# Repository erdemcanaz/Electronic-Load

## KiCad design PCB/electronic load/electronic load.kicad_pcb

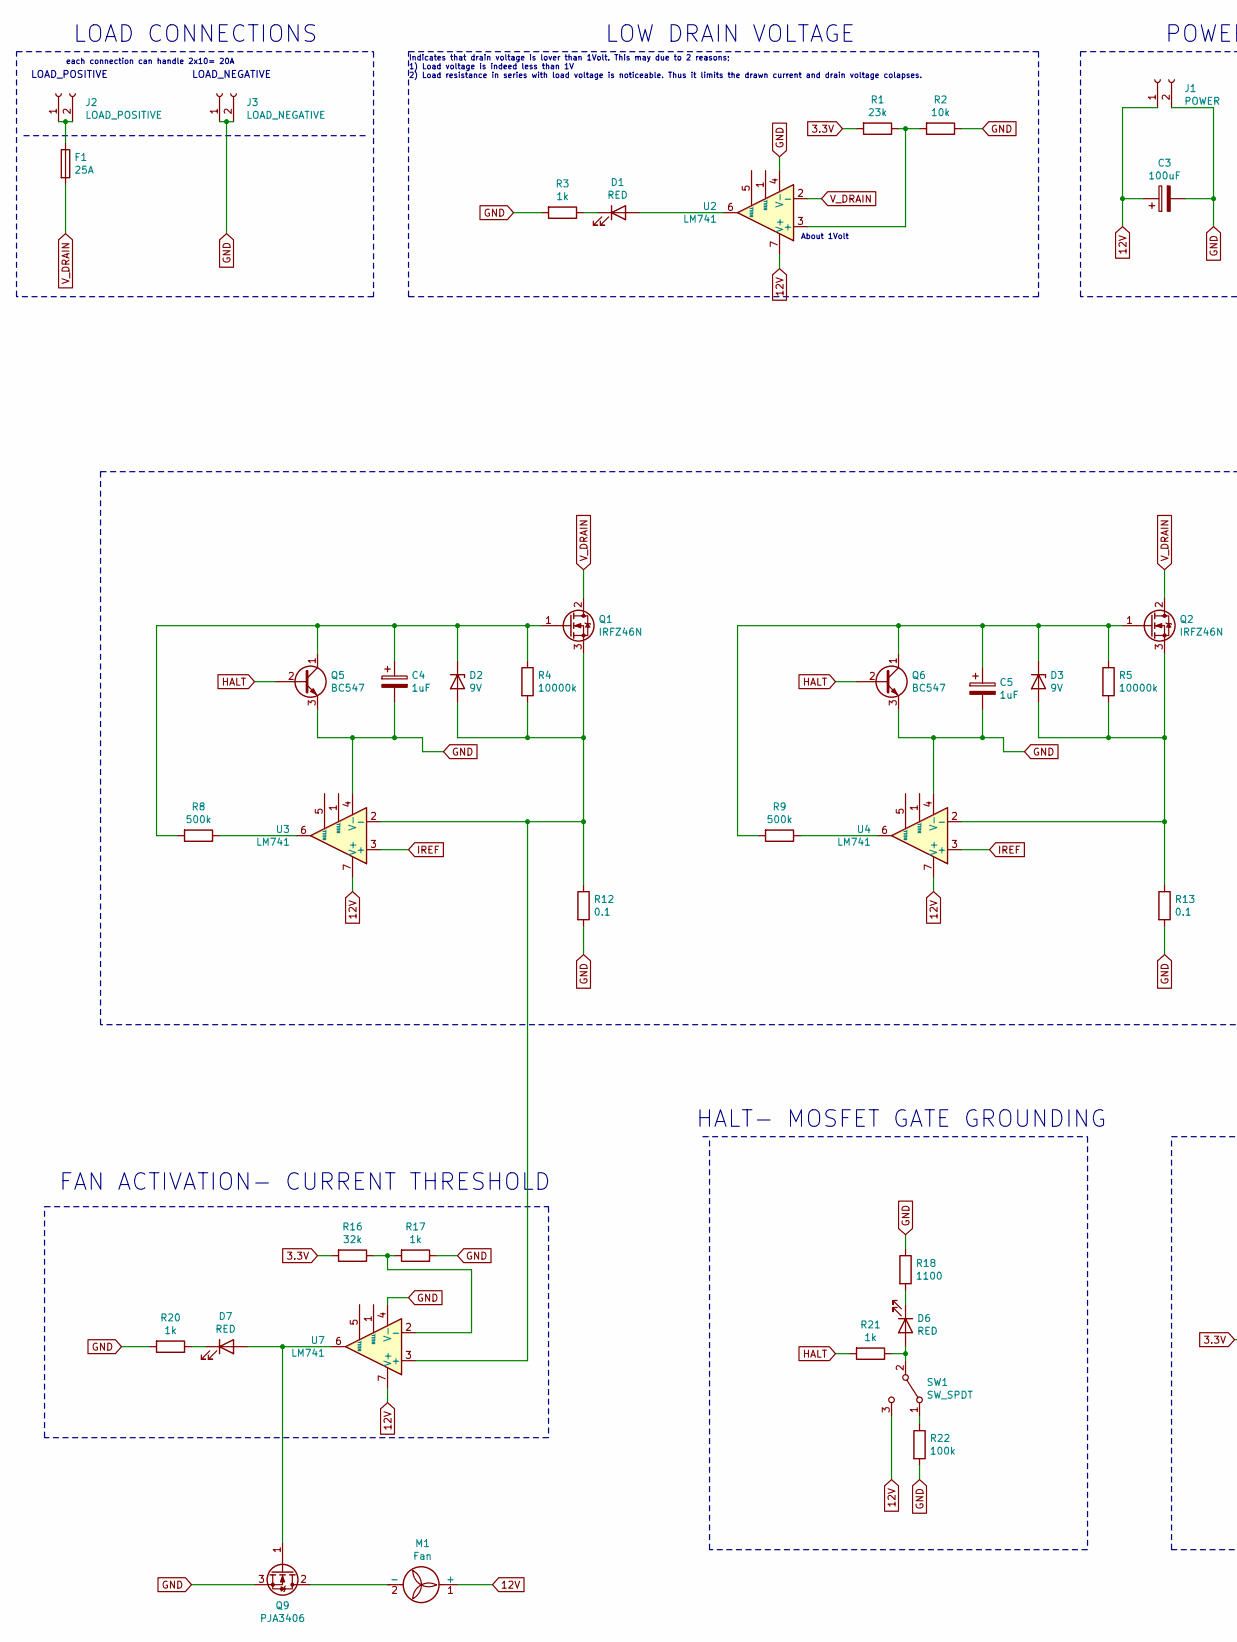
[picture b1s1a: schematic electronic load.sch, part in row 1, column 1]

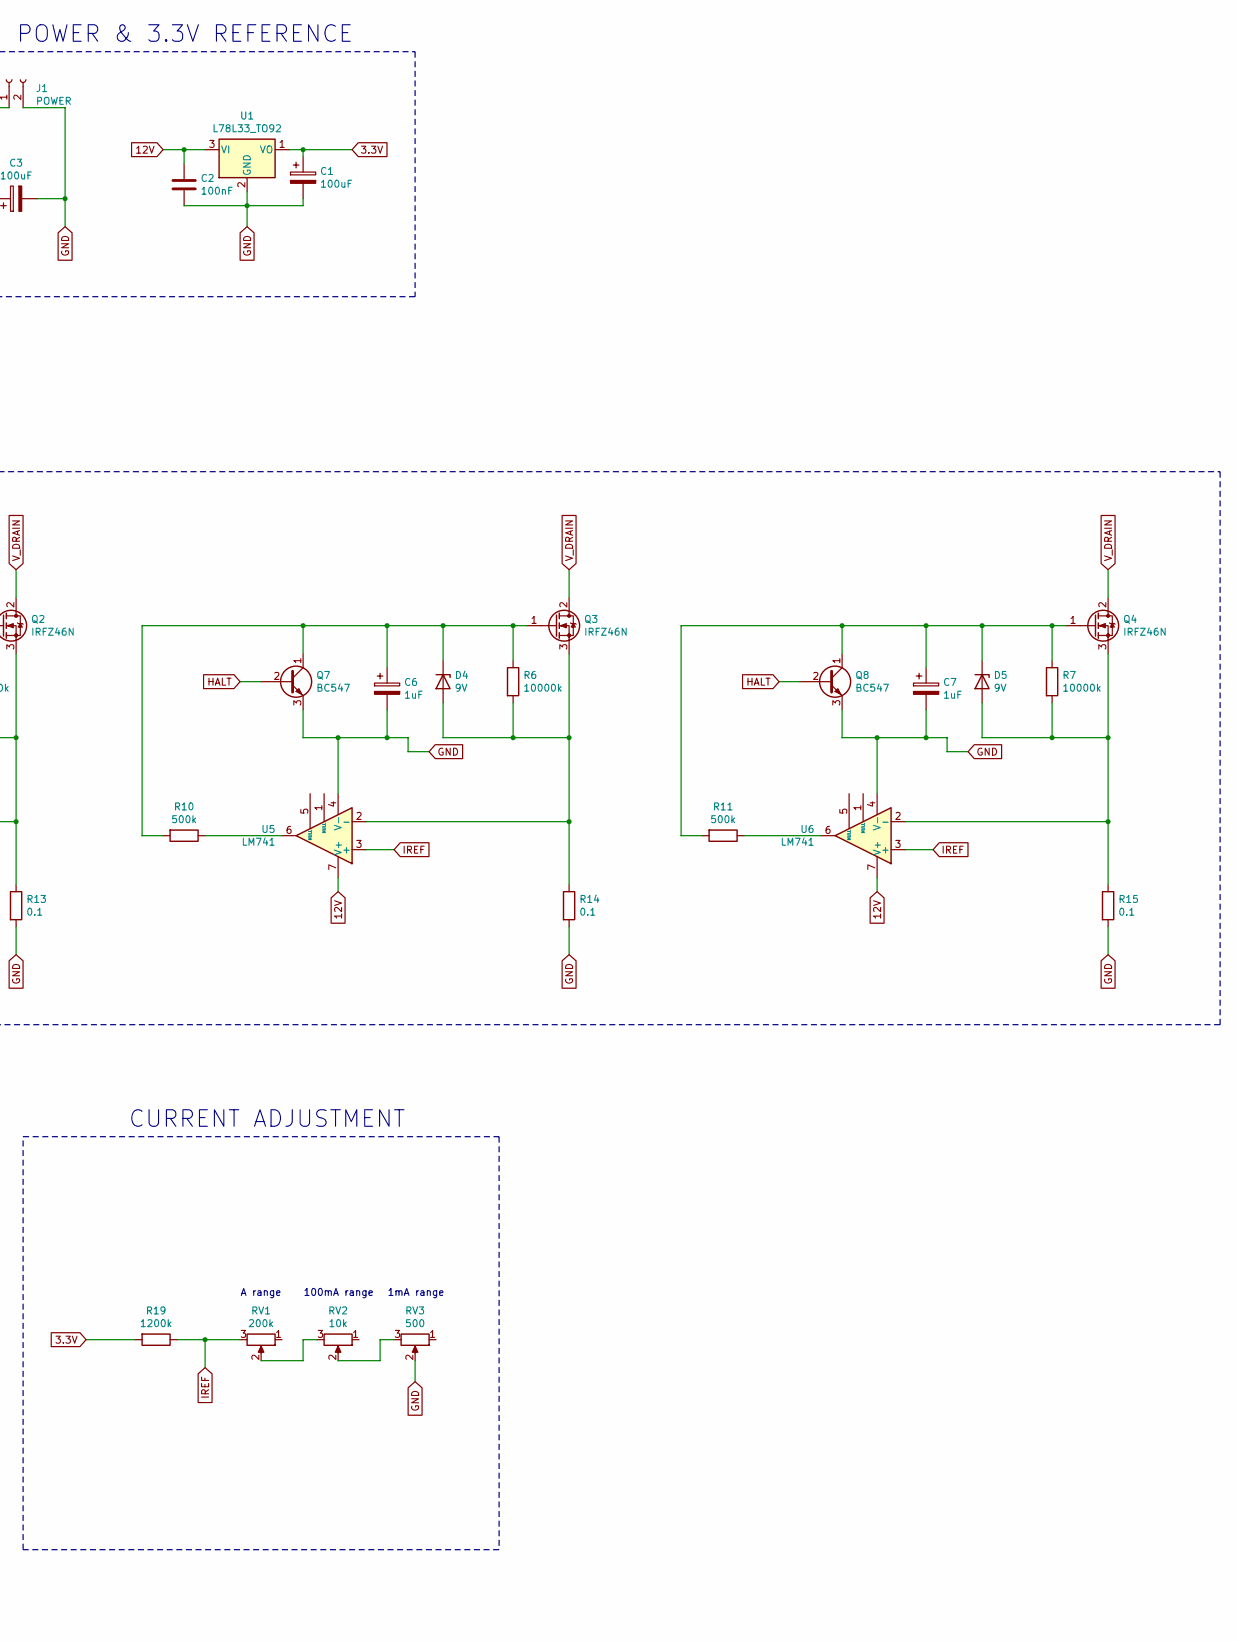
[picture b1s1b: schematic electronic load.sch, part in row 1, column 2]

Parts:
C1, C3: 100uF; CP_Radial_D5.0mm_P2.00mm
C2: 100nF; CP_Radial_D5.0mm_P2.00mm
C4, C5, C6, C7: 1uF; CP_Radial_D5.0mm_P2.00mm
D1, D6, D7: RED; LED_D3.0mm_FlatTop
D2, D3, D4, D5: 9V; D_A-405_P12.70mm_Horizontal
F1: 25A; fuse
J1: POWER; klemens 2li
J2: LOAD_POSITIVE; klemens 2li
J3: LOAD_NEGATIVE; klemens 2li
M1: Fan; PinHeader_1x02_P2.00mm_Vertical
Q1, Q2, Q3, Q4: IRFZ46N; TO-220-3_Horizontal_TabUp
Q5, Q6, Q7, Q8: BC547; TO-92_Inline_Wide
Q9: PJA3406; SOT-23
R1: 23k; R_Axial_DIN0207_L6.3mm_D2.5mm_P7.62mm_Horizontal
R2: 10k; R_Axial_DIN0207_L6.3mm_D2.5mm_P7.62mm_Horizontal
R3, R17, R20, R21: 1k; R_Axial_DIN0207_L6.3mm_D2.5mm_P7.62mm_Horizontal
R4, R5, R6, R7: 10000k; R_Axial_DIN0207_L6.3mm_D2.5mm_P7.62mm_Horizontal
R8, R9, R10, R11: 500k; R_Axial_DIN0207_L6.3mm_D2.5mm_P7.62mm_Horizontal
R12, R13, R14, R15: 0.1; R_Axial_Power_L25.0mm_W9.0mm_P27.94mm
R16: 32k; R_Axial_DIN0207_L6.3mm_D2.5mm_P7.62mm_Horizontal
R18: 1100; R_Axial_DIN0207_L6.3mm_D2.5mm_P7.62mm_Horizontal
R19: 1200k; R_Axial_DIN0207_L6.3mm_D2.5mm_P7.62mm_Horizontal
R22: 100k; R_Axial_DIN0207_L6.3mm_D2.5mm_P7.62mm_Horizontal
RV1: 200k; pot
RV2: 10k; pot
RV3: 500; pot
SW1: SW_SPDT; PinHeader_1x03_P2.00mm_Horizontal
U1: L78L33_TO92; TO-92_Inline_Wide
U2, U3, U4, U5, U6, U7: LM741; DIP-8_W7.62mm

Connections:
3.3V: C1.1, R1.2, R16.2, R19.2, U1.1 (VO)
12V: C2.1, C3.1, J1.1, M1.1 (+), SW1.3 (C), U1.3 (VI), U2.7 (V+), U3.7 (V+), U4.7 (V+), U5.7 (V+), U6.7 (V+), U7.7 (V+)
GND: C1.2, C2.2, C3.2, C4.2, C5.2, C6.2, C7.2, J1.2, J3.1, J3.2, Q5.3 (E), Q6.3 (E), Q7.3 (E), Q8.3 (E), Q9.3 (S), R2.1, R3.2, R12.2, R13.2, R14.2, R15.2, R17.1, R18.1, R20.2, R22.2, RV3.2, U1.2 (GND), U2.4 (V-), U3.4 (V-), U4.4 (V-), U5.4 (V-), U6.4 (V-), U7.4 (V-)
HALT: Q5.2 (B), Q6.2 (B), Q7.2 (B), Q8.2 (B), R21.2
IREF: R19.1, RV1.3, U3.3 (+), U4.3 (+), U5.3 (+), U6.3 (+)
unnamed: C4.1, D2.1 (K), Q1.1 (G), Q5.1 (C), R4.1, R8.2
unnamed: C5.1, D3.1 (K), Q2.1 (G), Q6.1 (C), R5.1, R9.2
unnamed: C6.1, D4.1 (K), Q3.1 (G), Q7.1 (C), R6.1, R10.2
unnamed: C7.1, D5.1 (K), Q4.1 (G), Q8.1 (C), R7.1, R11.2
unnamed: D1.1 (K), R3.1
unnamed: D1.2 (A), U2.6
unnamed: D2.2 (A), Q1.3 (S), R4.2, R12.1, U3.2 (-), U7.3 (+)
unnamed: D3.2 (A), Q2.3 (S), R5.2, R13.1, U4.2 (-)
unnamed: D4.2 (A), Q3.3 (S), R6.2, R14.1, U5.2 (-)
unnamed: D5.2 (A), Q4.3 (S), R7.2, R15.1, U6.2 (-)
unnamed: D6.1 (K), R18.2
unnamed: D6.2 (A), R21.1, SW1.2 (B)
unnamed: D7.1 (K), R20.1
unnamed: D7.2 (A), Q9.1 (G), U7.6
unnamed: F1.1, J2.1, J2.2
unnamed: M1.2 (-), Q9.2 (D)
unnamed: R1.1, R2.2, U2.3 (+)
unnamed: R8.1, U3.6
unnamed: R9.1, U4.6
unnamed: R10.1, U5.6
unnamed: R11.1, U6.6
unnamed: R16.1, R17.2, U7.2 (-)
unnamed: R22.1, SW1.1 (A)
unnamed: RV1.2, RV2.3
unnamed: RV2.2, RV3.3
V_DRAIN: F1.2, Q1.2 (D), Q2.2 (D), Q3.2 (D), Q4.2 (D), U2.2 (-)

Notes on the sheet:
LOAD_POSITIVE
LOAD_NEGATIVE
LOAD CONNECTIONS
LOW DRAIN VOLTAGE
Indicates that drain voltage is lover than 1Volt. This may due to 2 reasons; 1) Load voltage is indeed less than 1V 2) Load resistance in series with load voltage is noticeable. Thus it limits the drawn current and drain voltage colapses.
About 1Volt
FAN ACTIVATION- CURRENT THRESHOLD
POWER & 3.3V REFERENCE
HALT- MOSFET GATE GROUNDING
A range
100mA range
1mA range
CURRENT ADJUSTMENT
each connection can handle 2x10= 20A

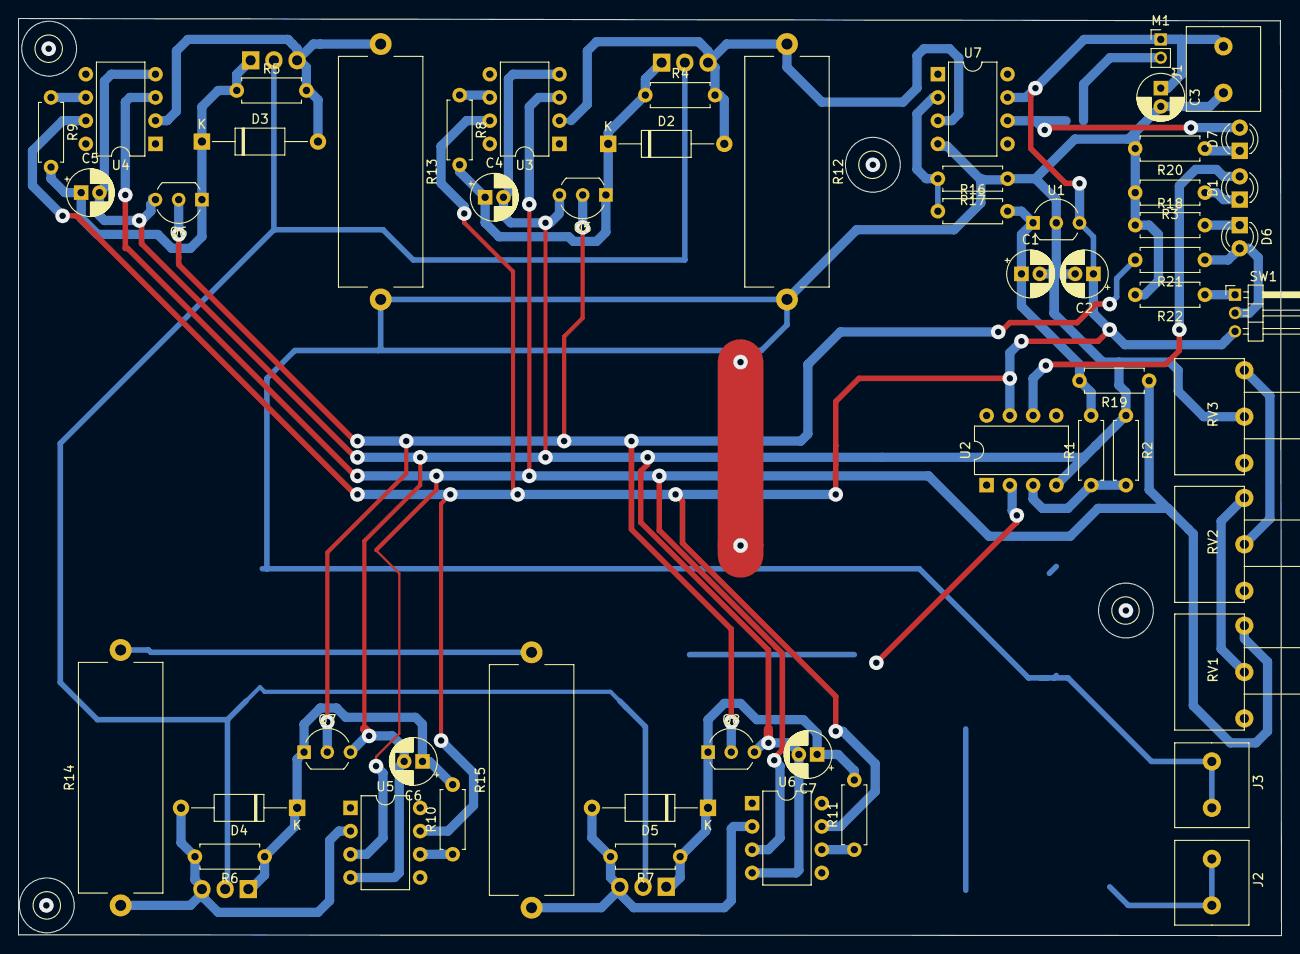
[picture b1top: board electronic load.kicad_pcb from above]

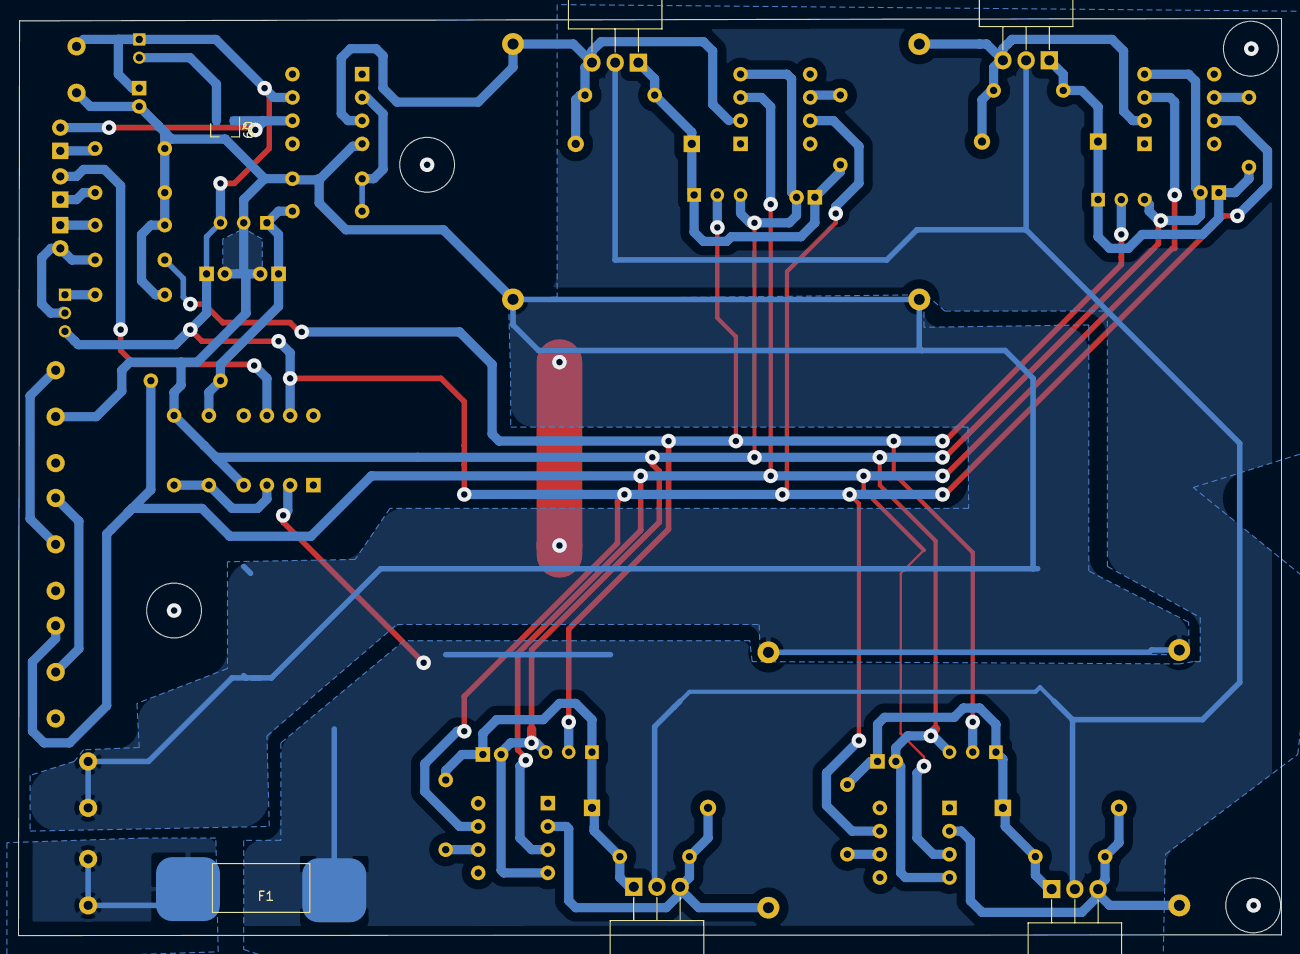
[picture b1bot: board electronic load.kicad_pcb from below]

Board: 2 copper layers, 138.2 x 100.3 mm, 61 parts (6 on the bottom side), 31 nets.

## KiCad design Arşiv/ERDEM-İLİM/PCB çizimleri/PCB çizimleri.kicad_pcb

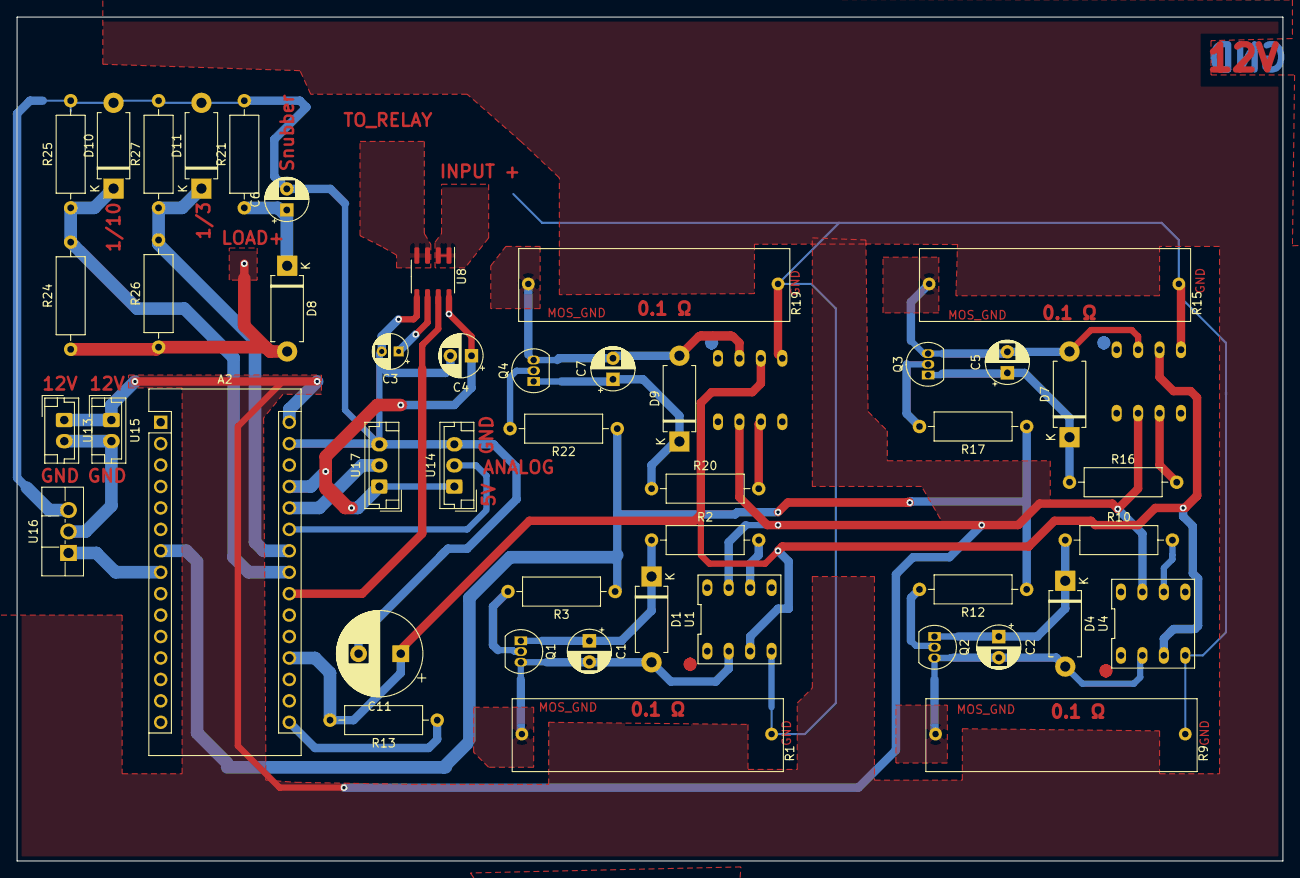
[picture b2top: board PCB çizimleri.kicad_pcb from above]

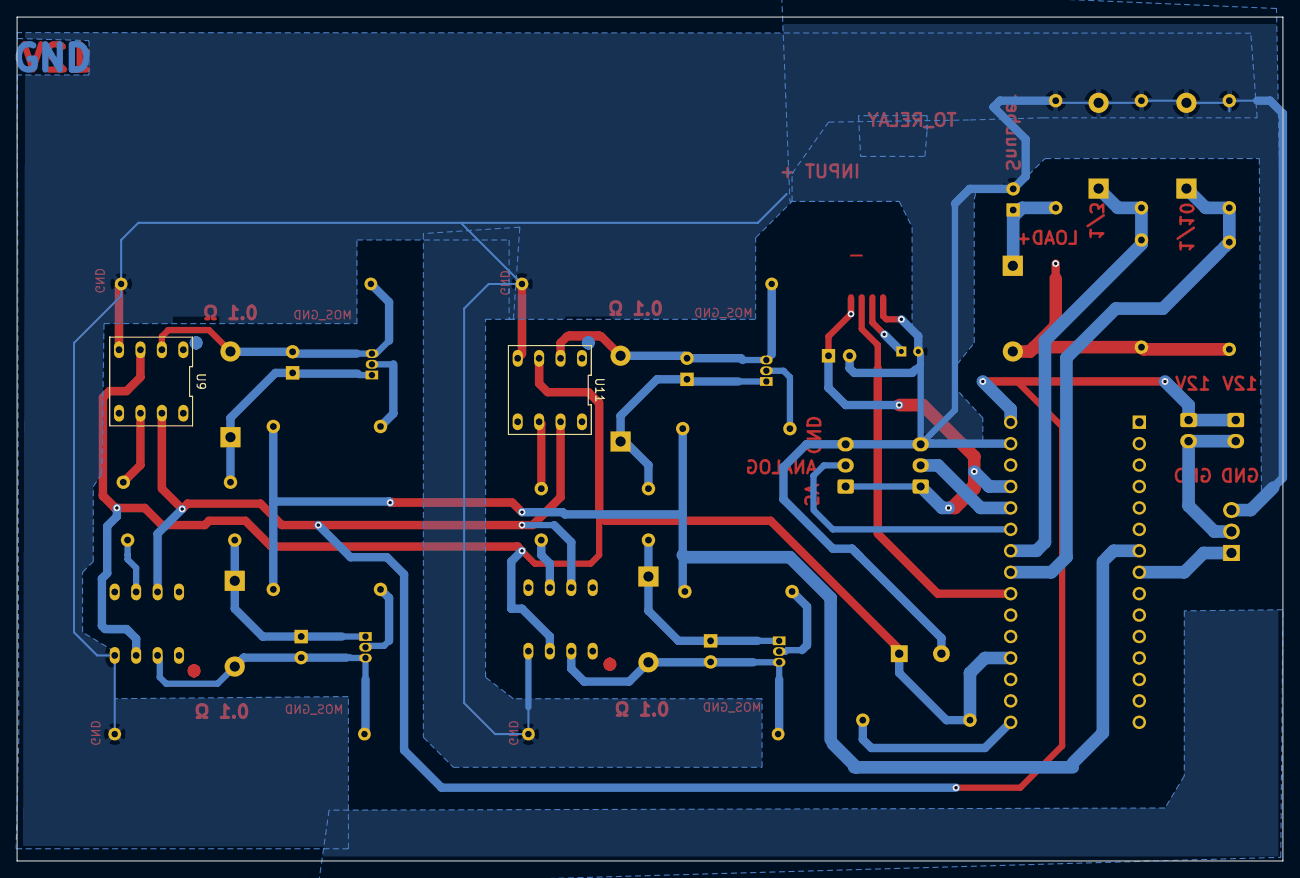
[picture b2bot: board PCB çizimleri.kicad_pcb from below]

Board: 2 copper layers, 150.0 x 100.0 mm, 48 parts (2 on the bottom side), 34 nets.

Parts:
A2: Arduino_Nano_v2.x; Arduino_Nano
C1, C2, C5, C7: 20uF; CP_Radial_D5.0mm_P2.50mm
C3: 1nF; CP_Radial_D4.0mm_P2.00mm
C4: 0.1uF; CP_Radial_D5.0mm_P2.50mm
C6: 100uF; CP_Radial_D5.0mm_P2.50mm
C11: 10uf; CP_Radial_D10.0mm_P5.00mm
D1, D4, D7, D9: 6.8; D_DO-15_P10.16mm_Horizontal
D8: D; D_DO-15_P10.16mm_Horizontal
D10, D11: 6.2V; D_DO-15_P10.16mm_Horizontal
Q1, Q2, Q3, Q4: BC547; TO-92_Inline
R1, R9, R15, R19: 0.1; 5W_tas
R2, R10, R16, R20: 330k; R_Axial_DIN0309_L9.0mm_D3.2mm_P12.70mm_Horizontal
R3, R12, R17, R22: 1k; R_Axial_DIN0309_L9.0mm_D3.2mm_P12.70mm_Horizontal
R13: 100k; R_Axial_DIN0309_L9.0mm_D3.2mm_P12.70mm_Horizontal
R21, R26: 20k; R_Axial_DIN0309_L9.0mm_D3.2mm_P12.70mm_Horizontal
R24: 36k; R_Axial_DIN0309_L9.0mm_D3.2mm_P12.70mm_Horizontal
R25: 4k; R_Axial_DIN0309_L9.0mm_D3.2mm_P12.70mm_Horizontal
R27: 10k; R_Axial_DIN0309_L9.0mm_D3.2mm_P12.70mm_Horizontal
U1, U4, U9, U11: LM741; DIP-8_296_ELL
U8: ACS712xLCTR-30A; SOIC-8_3.9x4.9mm_P1.27mm
U13, U15: fan; JST_EH_B2B-EH-A_1x02_P2.50mm_Vertical
U14, U17: LM35-LP; JST_EH_B3B-EH-A_1x03_P2.50mm_Vertical
U16: IRFZ44N; TO-220F-3_Vertical

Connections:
5V_ard: A2.27, C4.1, U8.8, U14.1, U17.1
12V: A2.30, U1.7, U4.7, U9.7, U11.7, U13.1, U15.1
CURRENT: A2.22, U8.7
D4: A2.7, R3.1, R12.1, R17.1, R22.1
D5: A2.8, U16.1
GND: A2.4, A2.29, C3.2, C4.2, C6.2, C11.2, D10.2, D11.2, R1.2, R9.2, R15.2, R19.2, R21.2, R25.2, R27.2, U1.4, U4.4, U8.5, U9.4, U11.4, U14.3, U16.3, U17.3
INPUT_+: U8.1, U8.2
LOAD_+: D8.2, R24.1, R26.1
unnamed: A2.16, R13.1
unnamed: C1.1, D1.1, Q1.1, R2.1
unnamed: C1.2, D1.2, Q1.3, R1.1, U1.2
unnamed: C2.1, D4.1, Q2.1, R10.1
unnamed: C2.2, D4.2, Q2.3, R9.1, U4.2
unnamed: C3.1, U8.6
unnamed: C5.1, D7.1, Q3.1, R16.1
unnamed: C5.2, D7.2, Q3.3, R15.1, U9.2
unnamed: C6.1, D8.1, R21.1
unnamed: C7.1, D9.1, Q4.1, R20.1
unnamed: C7.2, D9.2, Q4.3, R19.1, U11.2
unnamed: U8.3, U8.4
unnamed: Q1.2, R3.2
unnamed: Q2.2, R12.2
unnamed: Q3.2, R17.2
unnamed: Q4.2, R22.2
unnamed: R2.2, U1.6
unnamed: R10.2, U4.6
unnamed: R16.2, U9.6
unnamed: R20.2, U11.6
unnamed: U13.2, U15.2, U16.2
T1: A2.25, U14.2
T2: A2.26, U17.2
V_REF: A2.19, C11.1, R13.2, U1.3, U4.3, U9.3, U11.3
V_read_3: A2.24, D11.1, R26.2, R27.1
V_read_10: A2.23, D10.1, R24.2, R25.1

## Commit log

2020-10-22 Datasheet
    Datasheet of IRFZ46N is added
2020-10-22 Datasheet
    ATMEGA-328P
2020-10-23 DATASHEET
    LTspice-opamp model
2020-10-23 test
    test ettim
2020-10-23 yaptım
2020-10-23 Düzenleme
    Gülce; denemek için yüklediğimiz bazı dosyaları sildim ve kendime ait bir dosya açtım.
2020-10-23 Düzenleme2
    adımıza dosy açtım
2020-10-25 LT Spice simulations
    we have worked on some circuits enables us to control;
    1) current in R circuits
    2) current in RL circuits
    3) Reverse & low voltage protection
2020-10-25 Relay circuit feature
    Now relays turn on quickly however it turns of slowly over 330k resistor (about 3.5s to turn of). Thus, one may use voltage sources where voltage alternates between 0-48V
2020-10-25 Design paramaters
    40A-48V-400Watt DC
2020-10-25 Design parameters
    Design different voltage dividers for Ardino analog read
2020-10-26 Build Of Materials-BOM
    1-BOM list is created
    2- some youtube videos are added
2020-10-26 design parameters
    detailed
2020-10-27 CURRENT CONTROL FOR ALL LOAD WAWE FORMS
    Our previous designs for "mosfet gate voltage control with opamp according to current measurement" was not doing well with coils and others waweforms rather than pure DC. "In this commit I have added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
2020-10-28 REVERSE & LOW VOLTAGE PROTECTION
    floating votlage , Low voltage or negative voltage closese the relay and another opamp circuit holds it closed in 2ms electronical + Mechanical time until either
    1) User manually preses to the button
    2)Arduino shuts the safety( not obvious to all people who uses the device only to ones who read the manual)
    Also arduino may deliberately close the relay. (over voltage or some preparing)
    # ? # Why arduino may remove the protection ?
    Say we have a square wave: in such case the if frequency is increased opamp's output voltage decreases(bandwith) and triggers the safety feature {LOW DUTY PWM may also trigger } which turns off the r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
2020-10-28 REVERSE- FLOATING- LOW VOLTAGE PROTECTION
    floating votlage , Low voltage or negative voltage closese the relay and another opamp circuit holds it closed in 2ms electronical + Mechanical time until either
    1) User manually preses to the button
    2)Arduino shuts the safety( not obvious to all people who uses the device only to ones who read the manual)
    Also arduino may deliberately close the relay. (over voltage or some preparing)
    # ? # Why arduino may remove the protection ?
    Say we have a square wave: in such case the if frequency is increased opamp's output voltage decreases(bandwith) and triggers the safety feature {LOW DUTY PWM may also trigger } which turns off the r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
2020-11-07 Not important
2021-03-28 erdem-ilim
2021-03-29 .
    .
2021-03-29 schematic
    .
2021-12-24 BOM
    .
2021-12-25 PCB schematic
    .
2021-12-25 PCB-not complated
    .
2021-12-25 PCB- not finished
    .
2021-12-25 PCB finished
    .
